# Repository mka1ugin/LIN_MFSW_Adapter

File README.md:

# LIN_MFSW_Adapter

Проект адаптера для установки новых MQB мультирулей на автомобили платформы PQ.

Аппаратно адаптер выполнен на микроконтроллере STM32F103C8T6, схема и печатная плата разработаны в среде KiCad. Печатная плата односторонняя, габаритные размеры 43 x 26 мм.
В микроконтроллере задействованы 2 UART-порта, сконфигурированные в режиме LIN. UART1 работает в режиме Master и отправляет запросы на блок кнопок, UART2 в режиме Slave
обрабатывает запросы от подрулевого блока.
Прошивка написана в среде Keil 5 с использованием STM32Cube MX. Все действия выполняются в callback-функциях по окончании приёма/передачи по UART. 

Устройство испытано на VW Passat B6 с подрулевым блоком 5K0953569T (SW 0180) и мультирулём 5E3419093CVKH. Его кнопки максимально имитируют работу кнопок старого 12-кнопочного
руля. Кнопки вызова ассистентов, управления обогревом руля и включения круиза пока не задействованы.
Сам адаптер установлен прямо в мультируль, под него вырезано место (на версиях мультируля с датчиками KLR здесь установлен контроллер KLR).

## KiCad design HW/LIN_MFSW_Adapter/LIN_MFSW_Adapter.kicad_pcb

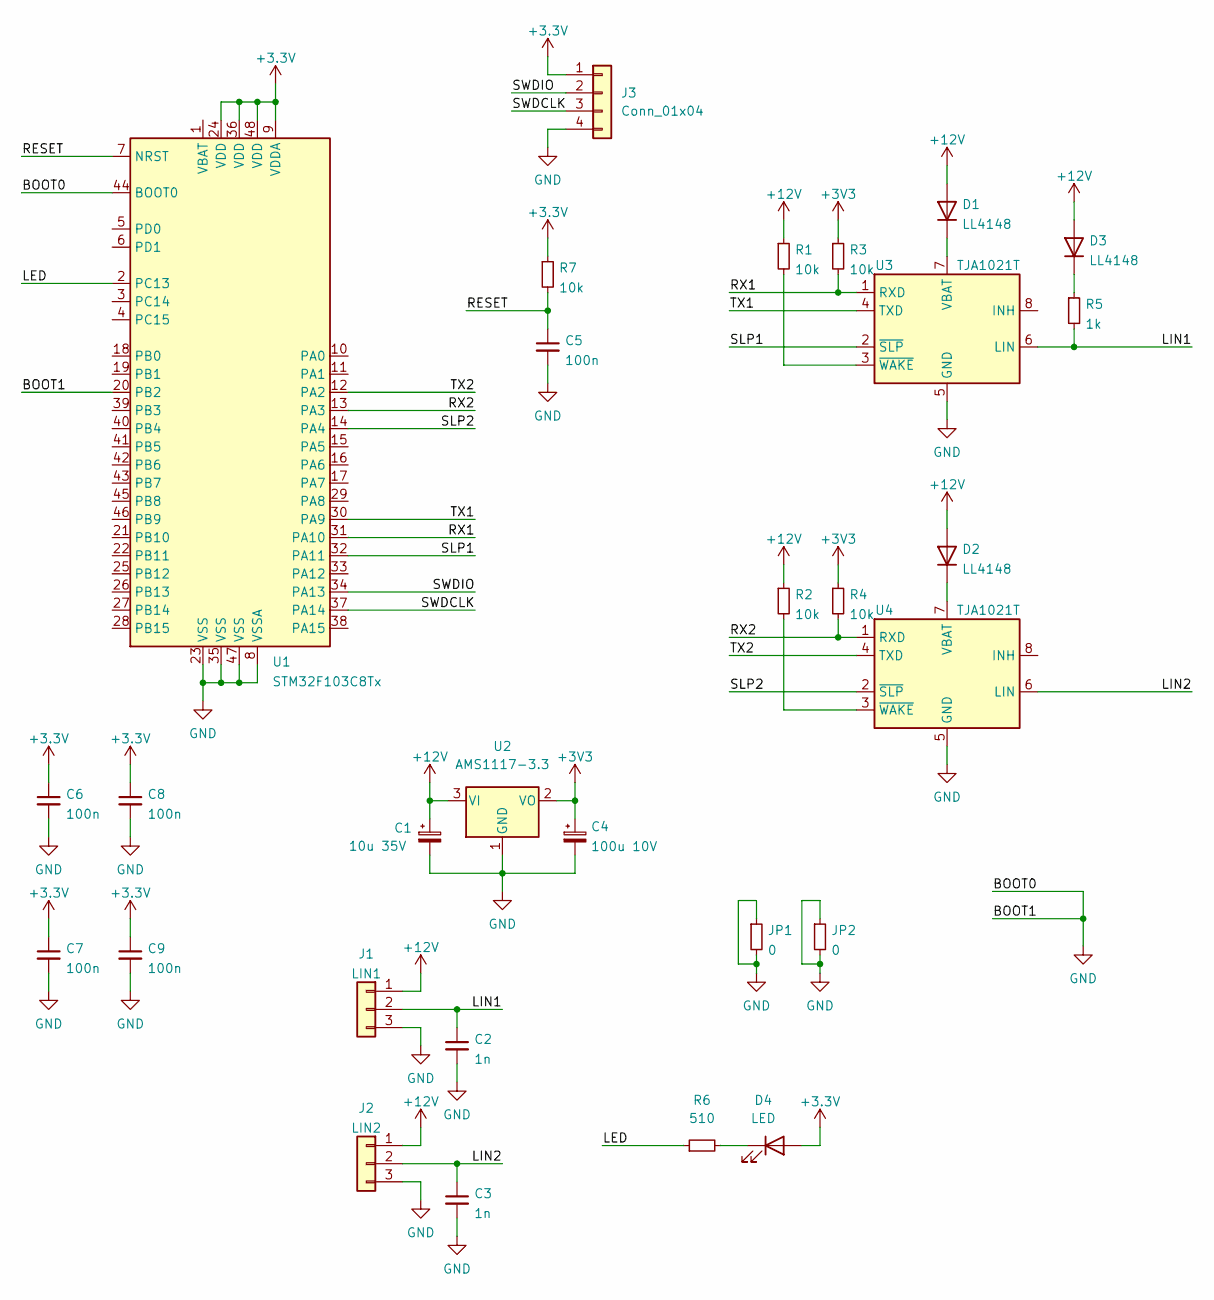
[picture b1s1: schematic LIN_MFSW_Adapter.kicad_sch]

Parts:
C1: 10u 35V; CP_EIA-7343-31_Kemet-D_Pad2.25x2.55mm_HandSolder
C2, C3: 1n; C_0805_2012Metric_Pad1.18x1.45mm_HandSolder
C4: 100u 10V; CP_EIA-7343-31_Kemet-D_Pad2.25x2.55mm_HandSolder
C5, C6, C7, C8, C9: 100n; C_0805_2012Metric_Pad1.18x1.45mm_HandSolder
D1, D2, D3: LL4148; D_MiniMELF
D4: LED; LED_1206_3216Metric_Pad1.42x1.75mm_HandSolder
J1: LIN1; PinHeader_1x03_P2.54mm_Vertical
J2: LIN2; PinHeader_1x03_P2.54mm_Vertical
J3: Conn_01x04; JTAG_SMD_CONNECTOR
JP1, JP2: 0; R_1206_3216Metric_Pad1.30x1.75mm_HandSolder
R1, R2, R3, R4, R7: 10k; R_0805_2012Metric_Pad1.20x1.40mm_HandSolder
R5: 1k; R_0805_2012Metric_Pad1.20x1.40mm_HandSolder
R6: 510; R_0805_2012Metric_Pad1.20x1.40mm_HandSolder
U1: STM32F103C8Tx; LQFP-48_7x7mm_P0.5mm
U2: AMS1117-3.3; SOT-223-3_TabPin2
U3, U4: TJA1021T; SOIC-8_3.9x4.9mm_P1.27mm

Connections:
+12V: C1.1, D1.2 (A), D2.2 (A), D3.2 (A), J1.1, J2.1, R1.1, R2.1, U2.3 (VI)
/LED: R6.1, U1.2 (PC13)
/LIN1: C2.1, J1.2, R5.2, U3.6 (LIN)
/LIN2: C3.1, J2.2, U4.6 (LIN)
/RESET: C5.1, R7.2, U1.7 (NRST)
/RX1: R3.2, U1.31 (PA10), U3.1 (RXD)
/RX2: R4.2, U1.13 (PA3), U4.1 (RXD)
/SLP1: U1.32 (PA11), U3.2 (~SLP)
/SLP2: U1.14 (PA4), U4.2 (~SLP)
/SWDCLK: J3.3, U1.37 (PA14)
/SWDIO: J3.2, U1.34 (PA13)
/TX1: U1.30 (PA9), U3.4 (TXD)
/TX2: U1.12 (PA2), U4.4 (TXD)
GND: C1.2, C2.2, C3.2, C4.2, C5.2, C6.2, C7.2, C8.2, C9.2, J1.3, J2.3, J3.4, JP1.1, JP1.2, JP2.1, JP2.2, U1.8 (VSSA), U1.20 (PB2), U1.23 (VSS), U1.35 (VSS), U1.44 (BOOT0), U1.47 (VSS), U2.1 (GND), U3.5 (GND), U4.5 (GND)
unnamed: D1.1 (K), U3.7 (VBAT)
unnamed: D2.1 (K), U4.7 (VBAT)
unnamed: D3.1 (K), R5.1
unnamed: D4.1 (K), R6.2
unnamed: R1.2, U3.3 (~WAKE)
unnamed: R2.2, U4.3 (~WAKE)

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
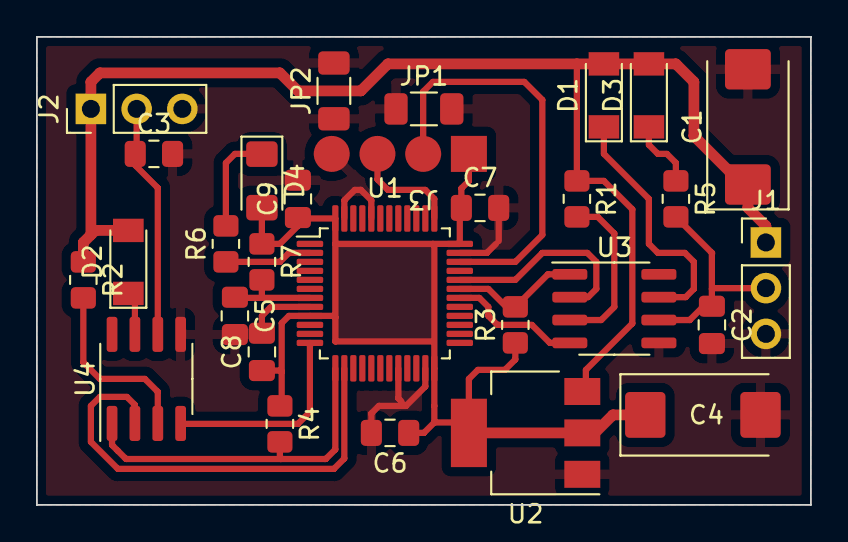
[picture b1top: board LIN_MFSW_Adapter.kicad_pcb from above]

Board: 2 copper layers, 43.0 x 26.0 mm, 29 parts (0 on the bottom side), 21 nets.

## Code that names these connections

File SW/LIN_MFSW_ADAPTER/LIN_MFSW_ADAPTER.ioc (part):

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Mcu.Name=STM32F103C(8-B)Tx
Mcu.Package=LQFP48
Mcu.UserName=STM32F103C8Tx
PA10.Mode=LIN
PA10.Signal=USART1_RX
PA11.GPIOParameters=GPIO_PuPd,GPIO_Label
PA11.GPIO_Label=SLP1
PA11.GPIO_PuPd=GPIO_PULLUP
PA11.Signal=GPIO_Output
PA13.Mode=Serial_Wire
PA13.Signal=SYS_JTMS-SWDIO
PA14.Mode=Serial_Wire
PA14.Signal=SYS_JTCK-SWCLK
PA2.Mode=LIN
PA2.Signal=USART2_TX
PA3.Mode=LIN
PA3.Signal=USART2_RX
PA4.GPIOParameters=GPIO_PuPd,GPIO_Label
PA4.GPIO_Label=SLP2
PA4.GPIO_PuPd=GPIO_PULLUP
PA4.Signal=GPIO_Output
PA9.Mode=LIN
PA9.Signal=USART1_TX
PB3.Signal=SYS_JTDO-TRACESWO
PC13-TAMPER-RTC.GPIOParameters=GPIO_Label
PC13-TAMPER-RTC.GPIO_Label=Led
PC13-TAMPER-RTC.Signal=GPIO_Output
PD0-OSC_IN.Mode=HSE-External-Oscillator
PD0-OSC_IN.Signal=RCC_OSC_IN
PD1-OSC_OUT.Mode=HSE-External-Oscillator
PD1-OSC_OUT.Signal=RCC_OSC_OUT
RCC.SYSCLKFreq_VALUE=64000000
RCC.SYSCLKSource=RCC_SYSCLKSOURCE_PLLCLK
board=custom
